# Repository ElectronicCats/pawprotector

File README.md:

# Paw Protector

The **Paw Protector** by **Electronic Cats** is a device specifically designed to protect the USB port of electronic devices, such as smartphones and tablets, when used in environments at risk of malicious devices like keyloggers or physical damage from devices like USB Killers. This accessory acts as a "physical fuse" that prevents data exchange and only allows power transmission, negotiating with the host device to achieve the maximum possible charging power.

### Key Features:
- **Compact and lightweight design:** Easy to install in any setup without taking up extra space.  
- **Universal compatibility:** Works with a wide range of devices with USB ports.  
- **Damage prevention:** Reduces the risk of malicious devices and physical threats to USB ports.  

- Attach between your USB cable and charger to physically block data transfer / syncing. Charge mobile devices without any pop-ups or risk of hacking / downloading viruses in cars, airports etc
- Our SmartCharge chip automatically switches between Apple, Universal and Samsung standards to ensure compatibility with your device and charge at up to 2.4A
- This is our USB-A to A model.
- Paw Protector protects your mobile data from being accidentally shared, stolen, or infected with malware! Paw Protector only transfers power, not your privacy!
- Completely open source

<p align=center><b>Where to buy and learn more</b></p>
<p align=center>

</p>

<p align=center>
  
</p>

## Wiki

For more details, please see the [Wiki](https://github.com/ElectronicCats/pawprotector/wiki) section.

## How to contribute 
 Contributions are welcome! 

Please read the document  [**Contribution Manual**](https://github.com/ElectronicCats/electroniccats-cla/blob/main/electroniccats-contribution-manual.md)  which will show you how to contribute your changes to the project.

✨ Thanks to all our [contributors](https://github.com/ElectronicCats/Cat-Sink/graphs/contributors)! ✨

See [**_Electronic Cats CLA_**](https://github.com/ElectronicCats/electroniccats-cla/blob/main/electroniccats-cla.md) for more information.

See the  [**community code of conduct**](https://github.com/ElectronicCats/electroniccats-cla/blob/main/electroniccats-community-code-of-conduct.md) for a vision of the community we want to build and what we expect from it."			

## License

Electronic Cats invests time and resources providing this open source design, please support Electronic Cats and open-source hardware by purchasing products from Electronic Cats!

Designed by Electronic Cats.

Firmware released under an GNU AGPL v3.0 license. See the LICENSE file for more information.

Hardware released under an CERN Open Hardware Licence v1.2. See the [LICENSE_HARDWARE](https://github.com/ElectronicCats/pawprotector/blob/main/LICENSE_HARDWARE.md) file for more information.

Electronic Cats is a registered trademark, please do not use it if you sell these PCBs.

Jul 2023
 
## Maintainer

Electronic Cats invests time and resources providing this open source design, please support Electronic Cats and open-source hardware by purchasing products from Electronic Cats!

[Agregando el link como referencia]: <https://github.com/ElectronicCats/Template-Project-KiCAD-CI>

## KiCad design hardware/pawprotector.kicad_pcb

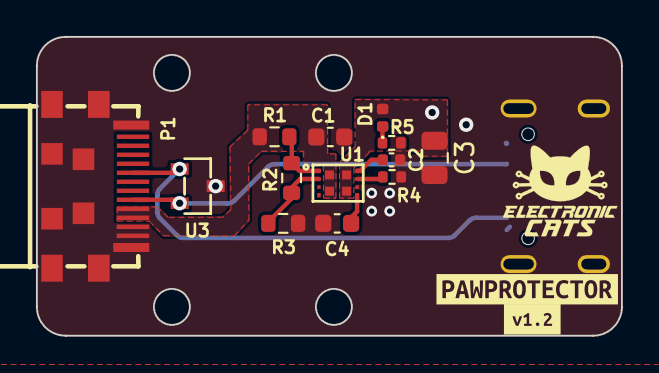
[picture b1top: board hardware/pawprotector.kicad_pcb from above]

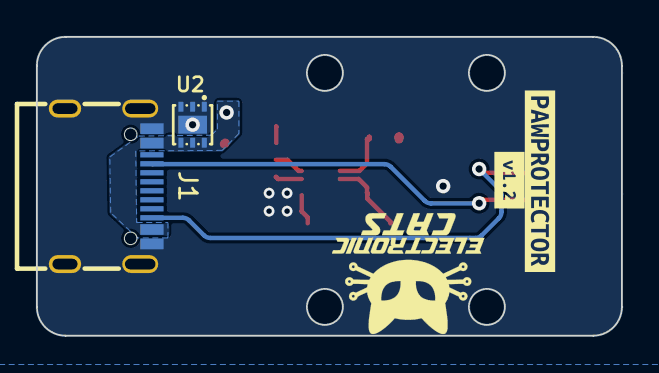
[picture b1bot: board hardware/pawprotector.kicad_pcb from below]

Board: 2 copper layers, 32.5 x 16.6 mm, 19 parts (4 on the bottom side), 11 nets.

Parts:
C1: 1uF; C_0603_1608Metric
C2: 12nF; C_0402_1005Metric
C3: 4.7uF; C_0805_2012Metric
C4: 10nF; C_0603_1608Metric
D1: ON; LED_0402_1005Metric
J1: USB_C_Receptacle; USB-C-SMD_KH-TYPE-C-16P
P1: USB_C_Plug; USB-C-SMD_TYPE-C-31-G-10
R1: 75k; R_0603_1608Metric
R2: 20.5k; R_0603_1608Metric
R3: 5k; R_0603_1608Metric
R4: 953; R_0402_1005Metric
R5: 1k; R_0402_1005Metric
U1: TPS259480AYWPR; POWERWCSP-12_L2.5-W1.7_TPS259482AYWPR
U2: TVS2200DRVR(ES); DFN-6_L2.0-W2.0-P0.65-BL-EP1.6
U3: ESD752DBZR; SOT-23-3_L2.9-W1.3-P1.90-LS2.4-BR
kibuzzard-6AC40DF5: G***; kibuzzard-6AC40DF5
kibuzzard-6AC515D0: G***; kibuzzard-6AC515D0
kibuzzard-65CAA4BB: G***; kibuzzard-65CAA4BB
kibuzzard-65CAA4FF: G***; kibuzzard-65CAA4FF

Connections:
+5V: C1.1, P1.A4 (VBUS), P1.B9 (VBUS), R1.1, U1.5 (VIN), U1.12 (VIN)
/CC1: J1.A5 (CC1), P1.A5 (CC), U3.2 (IO)
/CC2: J1.B5 (CC2), P1.B5 (VCONN), U3.1 (IO)
/ITIMER: C2.1, U1.10 (ITIMER)
/OVLO: R2.2, R3.1, U1.2 (OVLO)
/UVLO: R1.2, R2.1, U1.1 (EN/UVLO)
GND: C1.2, C2.2, C3.2, C4.2, J1.1, J1.2, J1.3, J1.4, J1.A1 (GND), J1.A12 (GND), J1.B1 (GND), J1.B12 (GND), P1.2, P1.3, P1.4, P1.5, P1.6, P1.7, P1.8, P1.9, P1.10, P1.A1 (GND), P1.B1 (GND), P1.B12 (GND), R3.2, R4.2, R5.2, U1.8 (GND), U2.1 (GND), U2.2 (GND), U2.3 (GND), U2.7 (EP), U3.3 (GND)
unnamed: D1.1 (K), R5.1
unnamed: C4.1, U1.7 (DVDT)
unnamed: R4.1, U1.9 (ILM)
VBUS: C3.1, D1.2 (A), J1.A4 (VBUS), J1.A9 (VBUS), J1.B4 (VBUS), J1.B9 (VBUS), U1.6 (VOUT), U1.11 (VOUT), U2.4 (VDD/IO), U2.5 (VDD/IO), U2.6 (VDD/IO)

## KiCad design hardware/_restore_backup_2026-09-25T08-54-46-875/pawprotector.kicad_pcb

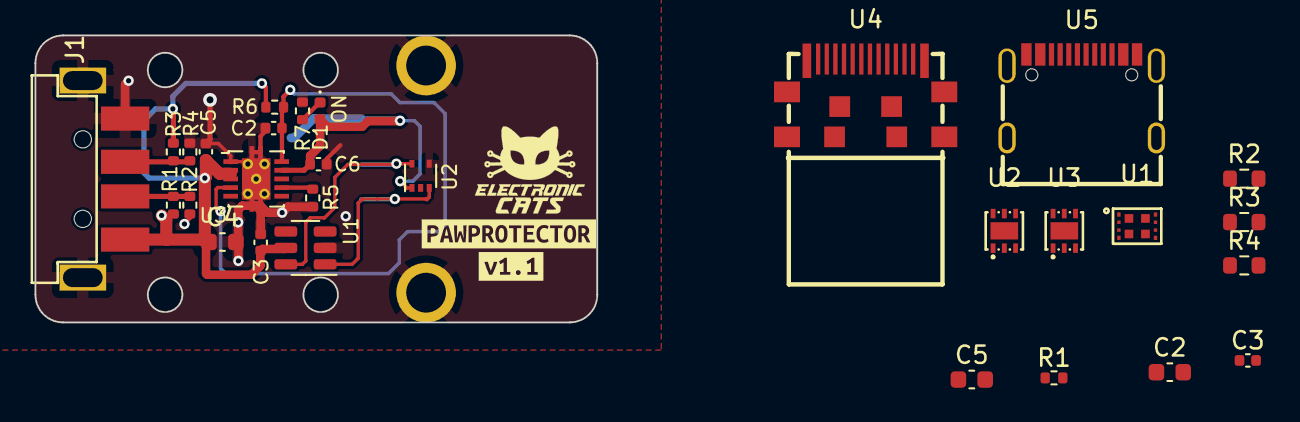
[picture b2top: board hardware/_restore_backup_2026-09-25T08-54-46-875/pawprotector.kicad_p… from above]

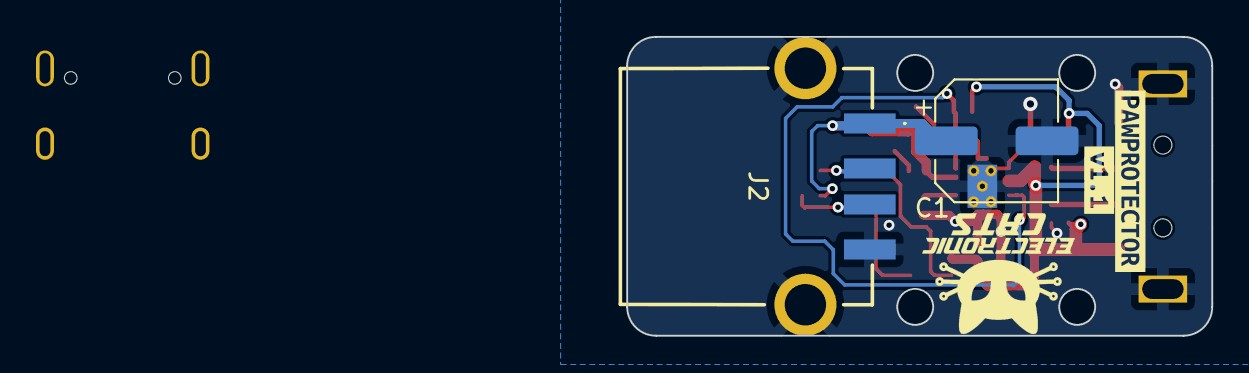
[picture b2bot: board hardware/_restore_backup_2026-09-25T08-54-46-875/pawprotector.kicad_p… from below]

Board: 2 copper layers, 32.5 x 16.6 mm, 35 parts (4 on the bottom side), 17 nets.

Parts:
C1: 150uF; CP_Elec_6.3x5.4
C2: 10nF; C_0603_1608Metric
C2#2: 0.22uF; C_0402_1005Metric
C3: 2.7nF; C_0402_1005Metric
C3#2, C5#2, C6: 0.1uF; C_0402_1005Metric
C4, C5: 1uF; C_0603_1608Metric
D1: ON; LED_0402_1005Metric
J1: USB_A; C46394
J2: USB_A; 875832010BLF
R1: 953; R_0402_1005Metric
R1#2: 43.2K; R_0402_1005Metric
R2: 75k; R_0603_1608Metric
R2#2, R4#2: 49.9K; R_0402_1005Metric
R3: 20.5k; R_0603_1608Metric
R3#2: 75K; R_0402_1005Metric
R4: 5k; R_0603_1608Metric
R5: 20K; R_0402_1005Metric
R6: 100K; R_0402_1005Metric
R7: 1K; R_0402_1005Metric
U1: TPS259480AYWPR; POWERWCSP-12_L2.5-W1.7_TPS259482AYWPR
U1#2: TPS2514A; SOT-23-6
U2: TPD2E001; SOT-553
U2#2, U3#2: TVS2200DRVR(ES); DFN-6_L2.0-W2.0-P0.65-BL-EP1.6
U3: TPS2561; VSON-10-1EP_3x3mm_P0.5mm_EP1.65x2.4mm_ThermalVias
U4: TYPE-C-31-G-10; USB-C-SMD_TYPE-C-31-G-10
U5: KH-TYPE-C-16P; USB-C-SMD_KH-TYPE-C-16P
kibuzzard-65CAA4BB: G***; kibuzzard-65CAA4BB
kibuzzard-65CAA4FF: G***; kibuzzard-65CAA4FF
kibuzzard-65CAA527: G***; kibuzzard-65CAA527
kibuzzard-65CAA533: G***; kibuzzard-65CAA533

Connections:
+5V: C3#2.1, C4.1, C5#2.1, J1.1 (VBUS), R1#2.1, R2.1, R3#2.1, R6.1, U1.5 (VIN), U1.12 (VIN), U1#2.5 (IN), U3.2 (IN), U3.3 (IN), U4.A4 (VBUS), U4.B9 (VBUS)
/CC1: U2#2.4 (VDD/IO), U2#2.5 (VDD/IO), U2#2.6 (VDD/IO), U4.A5 (CC), U5.A5 (CC1)
/CC2: U3#2.4 (VDD/IO), U3#2.5 (VDD/IO), U3#2.6 (VDD/IO), U4.B5 (VCONN), U5.B5 (CC2)
/D+: J2.3 (D+), U1#2.1 (DP1), U2.3 (IO1)
/D-: J2.2 (D-), U1#2.6 (DM1), U2.5 (IO2)
/DCP+: J1.3 (D+), R3#2.2, R4#2.1
/DCP-: J1.2 (D-), R1#2.2, R2#2.1
/FAULT: C2#2.1, R6.2, U3.4 (EN1), U3.10 (~FAULT1)
/ITIMER: C3.1, U1.10 (ITIMER)
/OVLO: R3.2, R4.1, U1.2 (OVLO)
/UVLO: R2.2, R3.1, U1.1 (EN/UVLO)
GND: C1.2, C2.2, C2#2.2, C3.2, C3#2.2, C4.2, C5.2, C5#2.2, C6.2, J1.4 (GND), J1.5 (Shield), J2.4 (GND), J2.5 (Shield), R1.2, R2#2.2, R4.2, R4#2.2, R5.2, R7.2, U1.8 (GND), U1#2.2 (GND), U2.4 (GND), U2#2.1 (GND), U2#2.2 (GND), U2#2.3 (GND), U2#2.7 (EP), U3.1 (GND), U3.11 (PAD), U3#2.1 (GND), U3#2.2 (GND), U3#2.3 (GND), U3#2.7 (EP), U4.2 (LATCH), U4.3 (GND), U4.A1 (GND), U4.B12 (GND), U5.1 (EP), U5.2 (EP), U5.3 (EP), U5.4 (EP), U5.A1 (GND), U5.A12 (GND), U5.B1 (GND), U5.B12 (GND)
unnamed: D1.1 (K), R7.1
unnamed: C2.1, U1.7 (DVDT)
unnamed: R1.1, U1.9 (ILM)
unnamed: R5.1, U3.7 (ILM)
VBUS: C1.1, C5.1, C6.1, D1.2 (A), J2.1 (VBUS), U1.6 (VOUT), U1.11 (VOUT), U2.1 (VCC), U3.9 (OUT1), U5.A4 (VBUS), U5.A9 (VBUS), U5.B4 (VBUS), U5.B9 (VBUS)

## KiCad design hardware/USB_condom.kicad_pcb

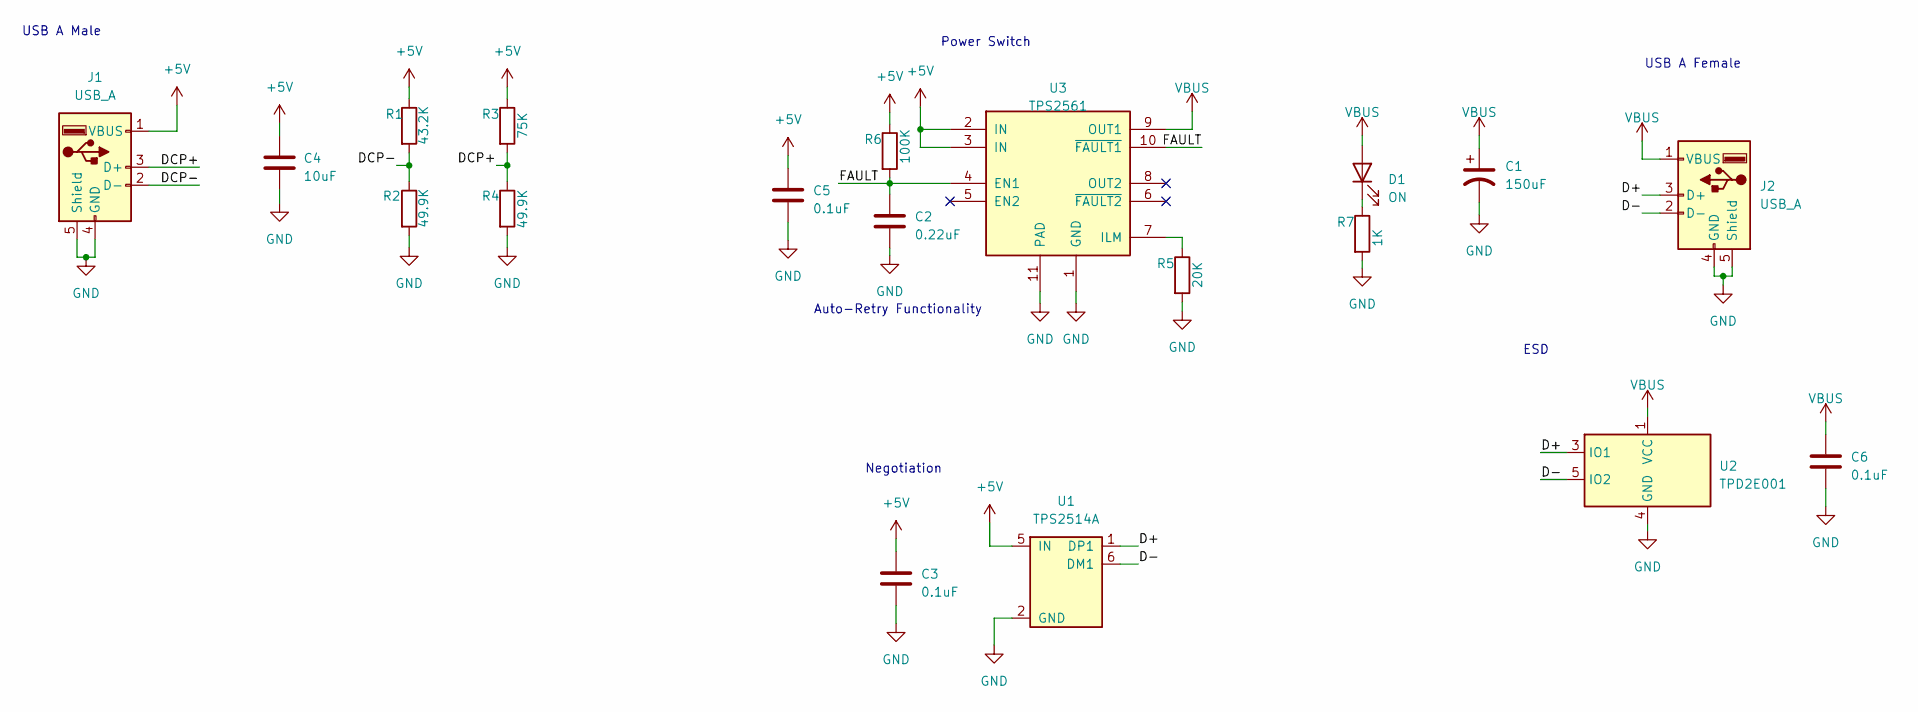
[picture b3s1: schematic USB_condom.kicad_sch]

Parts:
C1: 150uF; CP_Elec_6.3x5.4; LCSC# C2895744
C2: 0.22uF; C_0402_1005Metric; LCSC# C2903665
C3, C5, C6: 0.1uF; C_0402_1005Metric; LCSC# C392963
C4: 10uF; C_0805_2012Metric; LCSC# C3015160
D1: ON; LED_0402_1005Metric; LCSC# C965790
J1: USB_A; C46394; LCSC# C46394
J2: USB_A; 875832010BLF; LCSC# C599118
R1: 43.2K; R_0402_1005Metric; LCSC# C5356145
R2, R4: 49.9K; R_0402_1005Metric; LCSC# C2906873
R3: 75K; R_0402_1005Metric; LCSC# C3152096
R5: 20K; R_0402_1005Metric; LCSC# C100292
R6: 100K; R_0402_1005Metric; LCSC# C3152099
R7: 1K; R_0402_1005Metric; LCSC# C3152067
U1: TPS2514A; SOT-23-6; LCSC# C157567
U2: TPD2E001; SOT-553; LCSC# C150526
U3: TPS2561; VSON-10-1EP_3x3mm_P0.5mm_EP1.65x2.4mm_ThermalVias

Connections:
+5V: C3.1, C4.1, C5.1, J1.1 (VBUS), R1.1, R3.1, R6.1, U1.5 (IN), U3.2 (IN), U3.3 (IN)
/D+: J2.3 (D+), U1.1 (DP1), U2.3 (IO1)
/D-: J2.2 (D-), U1.6 (DM1), U2.5 (IO2)
/DCP+: J1.3 (D+), R3.2, R4.1
/DCP-: J1.2 (D-), R1.2, R2.1
/FAULT: C2.1, R6.2, U3.4 (EN1), U3.10 (~FAULT1)
GND: C1.2, C2.2, C3.2, C4.2, C5.2, C6.2, J1.4 (GND), J1.5 (Shield), J2.4 (GND), J2.5 (Shield), R2.2, R4.2, R5.2, R7.2, U1.2 (GND), U2.4 (GND), U3.1 (GND), U3.11 (PAD)
unnamed: D1.1 (K), R7.1
unnamed: R5.1, U3.7 (ILM)
VBUS: C1.1, C6.1, D1.2 (A), J2.1 (VBUS), U2.1 (VCC), U3.9 (OUT1)

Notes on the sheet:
USB A Female
Power Switch
Auto-Retry Functionality
ESD
Negotiation
USB A Male

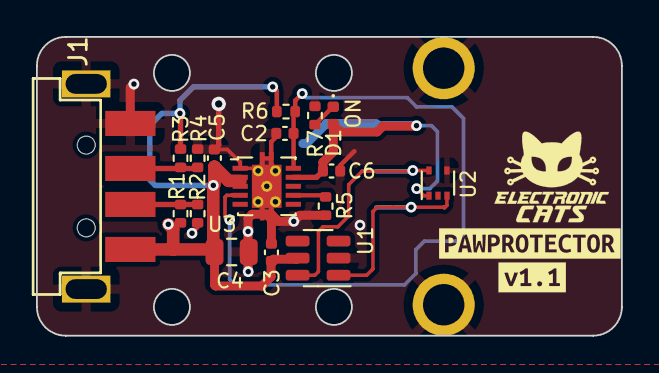
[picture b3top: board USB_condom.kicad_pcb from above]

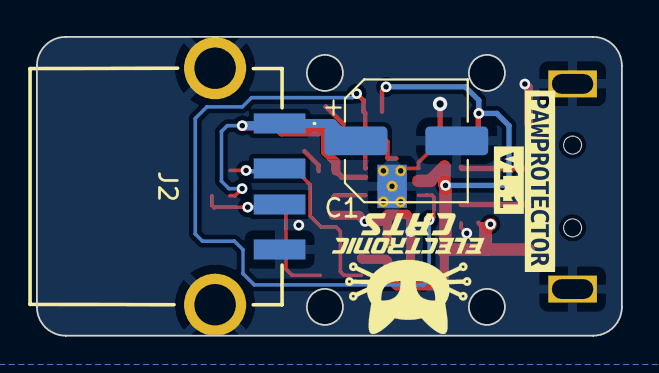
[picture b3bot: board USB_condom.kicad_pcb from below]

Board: 2 copper layers, 32.5 x 16.6 mm, 23 parts (4 on the bottom side), 10 nets.

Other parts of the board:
kibuzzard-65CAA4BB: G***; kibuzzard-65CAA4BB
kibuzzard-65CAA4FF: G***; kibuzzard-65CAA4FF
kibuzzard-65CAA527: G***; kibuzzard-65CAA527
kibuzzard-65CAA533: G***; kibuzzard-65CAA533

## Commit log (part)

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2023-02-01 First schematic from USB A to USB A
2023-03-27 Usb a-a, usb a-b upgrade
    Last update of the USB condom
2023-03-27 USB condom update
2023-04-19 update project add schematic and first layout
2023-04-19 update labels
2023-04-19 remove others files
2023-04-20 add capacitor, add LCSC numbers
2023-04-20 update pcb
2023-04-20 update gitignore
2023-06-13 add license
2023-06-13 Create LICENSE
2024-01-10 Pawprotector.step generated
2024-02-12 Move_Components
2024-02-19 BOM updated
2024-02-20 rename project
2024-04-11 feat(docs): Update README.md
    Add how to contribute
2024-04-24 feat(docs): add distributor button
2024-04-24 feat(docs): add text and distributor button
2024-11-25 feat: Update README.md
2025-03-28 feat(hw): case files
2025-06-17 feat(Hw):Bom_Updated
